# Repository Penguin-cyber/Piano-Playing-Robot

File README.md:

# Introduction

As someone who grew up playing the piano, I sometimes wish I could learn it more easily. Specifically, sometimes it would be helpful to have a physical example of how to play specific passages, even without a teacher. Hence, I came up with this idea: an anthropomorphic, piano-playing robot. There are many interesting ways robotic hands could be helpful to pianists. Although there are methods by which the piano can be played autonomously, these methods do not involve anthropomorphism.

Anthropomorphic robotic hands would provide an accurate reference that pianists
could use when learning various pieces. They would provide excellent utility for pianists
who wish to understand the technique and form required for challenging passages. Thus,
it serves as a powerful tool to accelerate piano mastery.

Another point is that anthropomorphic robotic hands could serve as a remote means for individuals to connect with each other. Even in isolation, pianists would be able to connect with others, potentially teleoperating the robotic hand to play with others. Moreover, this teleoperation could potentially be saved locally on the arm itself, enabling the widespread education and demonstration of how certain pieces may be played.

*Importantly, this project does not intend to replace human pianists. It simply serves as an aid for them to improve and dive deeper into their craft.*

The robot has an arm with 2 degrees of freedom (DOF), which rests on a rail with one DOF. Moreover, the hand itself has 10 DOF—that is, 2 DOF per finger, enabling each finger to yaw and pitch. In total, the system has 13 DOF, requiring 13 servo motors for actuation.

# Images

## Hand

## Forearm

## Base Arm

## Linear Slide

## Custom JST adapter board

# Wiring Diagram

# Bill of Materials
| PART	| QTY. |
| --------- | --- |
| 608 - 2RS Bearing| 28|
|3mm OD x 18mm pin|39|
|FeeTech Servo SCS15|3|
|50-37-5033|35|
|JST Adapter Board_PCB|5|
|Zeee 2S 5200mAh Lipo Battery 7.4V 50C	|1|
|LiPo 2S-3S Battery Balancer Charger|	1|
|FeeTech Servo SCS0009|	10|
|FE-URT-1|2|
|linear guide WS-10-40	|1|
|linear guide bearing WJ200UM-01-10	|4|
|PTFE Tubing	|1|
|Piscifun Lunker Braided Line - 40Lbs	|1|
|PLA	|4kg|

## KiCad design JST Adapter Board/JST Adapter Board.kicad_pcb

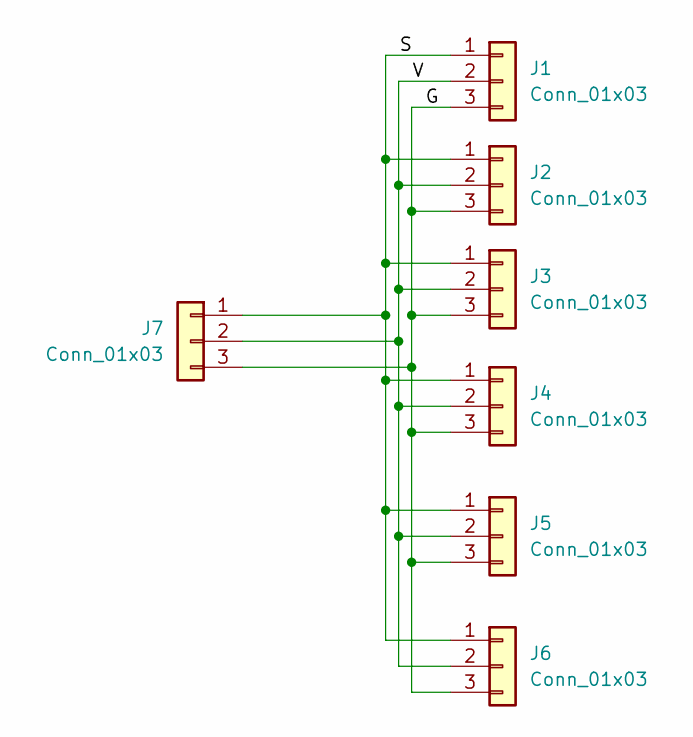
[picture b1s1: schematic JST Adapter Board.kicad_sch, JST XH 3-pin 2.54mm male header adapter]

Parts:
J1, J2, J3, J4, J5, J6, J7: Conn_01x03; JST_EH_B3B-EH-A_1x03_P2.50mm_Vertical

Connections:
/G: J1.3, J2.3, J3.3, J4.3, J5.3, J6.3, J7.3
/S: J1.1, J2.1, J3.1, J4.1, J5.1, J6.1, J7.1
/V: J1.2, J2.2, J3.2, J4.2, J5.2, J6.2, J7.2

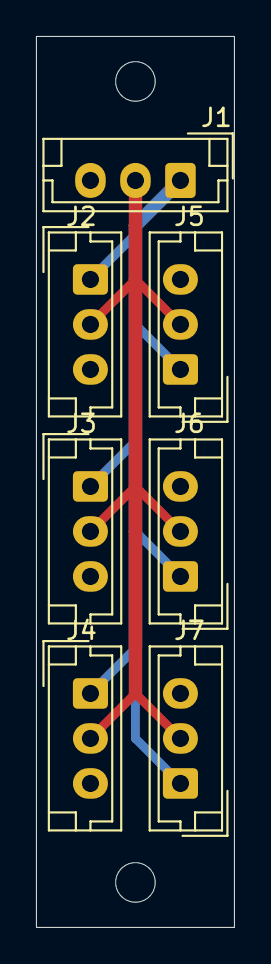
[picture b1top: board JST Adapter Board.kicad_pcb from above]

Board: 2 copper layers, 11.0 x 49.5 mm, 7 parts (0 on the bottom side), 3 nets.

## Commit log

2025-06-11 June 10
2025-06-12 June 11
2025-07-09 Create a
